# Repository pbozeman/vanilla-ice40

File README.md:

# Vanilla ICE40

Hardware design and verilog sample files for Lattice ICE40
development boards and expansion boards.

## Development Boards

There are 2 core boards, one based on an ICE40 HX4K with 96
available IO pins, and another based on an ICE40 HX8K with
192 available IO pins.

The core boards are "vanilla" with minimal on board peripherals.
Almost all IO pins are routed to mezzanine connectors. Expansion
boards can be mixed and matched for different projects, while reusing
the core board. The expansion boards can be daisy chained.

This is a work in progress for use in a personal project, but so far
the following boards are in the repo:

* **vanilla-ice40**: core board based on the HX4K TQ144 package. There is
an onboard USBC connector for power, programming, and uart/com port
communication. It is directly programmable with Lattice Diamond Programmer
and icestorm. The onboard FTDI chip can be disabled. The SPI pins to the
flash and ice40 are exposed if one wishes to use an external
programmer. There are 2 onboard user LEDs, 1 I2C connector, and 96 IOs
routed to a mezzanine connector on the right side of the board.

* **vanilla-ice40-hx8k**: core board based on the HX8K CT256 BGA package.
It is similar to the board above, but ads a user button on board. It has
192 available IO pins, with 96 IO pins routed to the left and 96 pins routed
to the right of the board. (A PCF file is provided for both boards, sharing
the same signal names for the right side of the board.)

* **breakout-sram**: 16Mbit sram chip with with mezzanine connectors
on both side of the board for pass through of unused pins.

* **breakout-pmod**: 12 port pmod connector, spaced such that they
can be used in single, dual or quad pmod configurations.

* **breakout-passthrough**: direct passthrough of all signals. (This
is basically a template and for testing.) NOTE: the net names and
labels on this board are stale.

Parts numbers are populated for Digikey and JLCPCB, and JLCPCB
rotations are provided. The bom and positions file, along with
gerbers, can be exported with the JLCPCB Fabrication Toolkit
plugin.

All boards other than the HX8K are single sided and optimized for cost
and hand assembly. My soldering skills are below average, and I manged to
hand assemble versions of each of these these boards other than the HX8K.
The HX8K uses BGA, via-in-pad, and 201 sized caps between the BGA pads, and
likely requires higher soldering skills.

## Verilog examples

* Verilog development has moved to <https://github.com/pbozeman/svc> for the core
SVC library, and <https://github.com/pbozeman/svc-example> for examples using
these boards.

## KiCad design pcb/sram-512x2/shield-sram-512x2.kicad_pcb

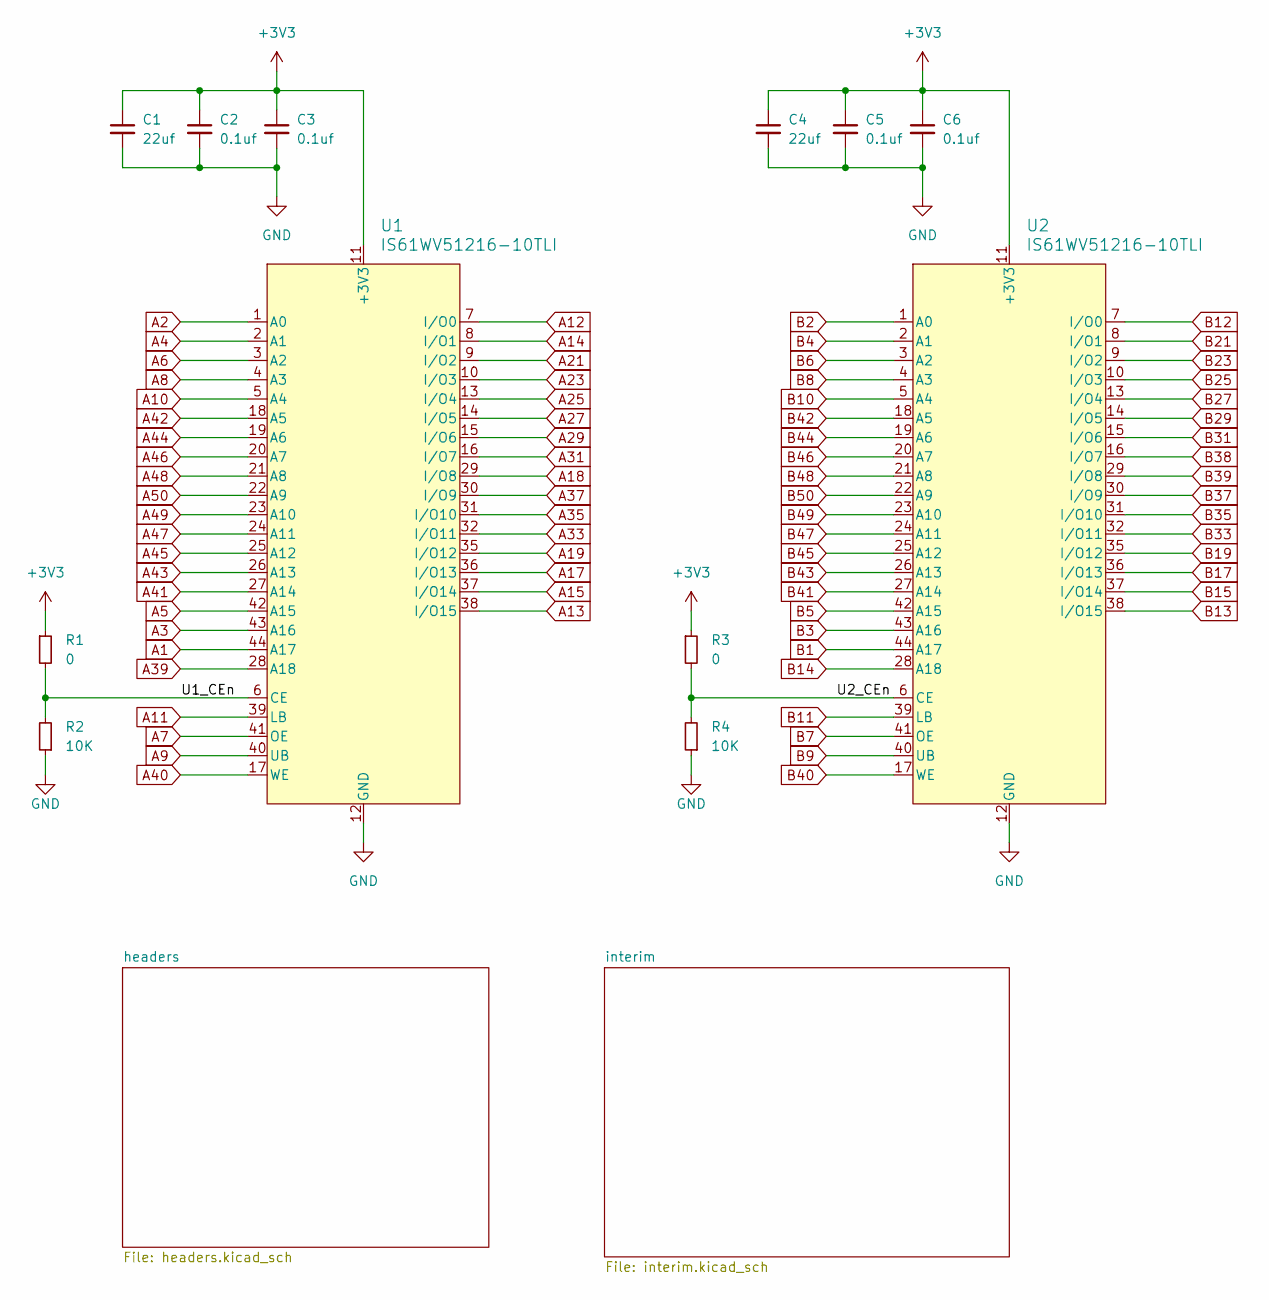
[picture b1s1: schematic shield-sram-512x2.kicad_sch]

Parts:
C1, C4: 22uf; C_0603_1608Metric; LCSC Part # C59461
C2, C3, C5, C6: 0.1uf; C_0402_1005Metric; LCSC Part # C1525
R1, R3: 0; R_0603_1608Metric; LCSC Part # DNP
R2, R4: 10K; R_0603_1608Metric; LCSC Part # C25804
U1, U2: IS61WV51216-10TLI; 44L_TSOP-2_400_ISI; LCSC Part # C397874

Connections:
+3V3: C1.1, C2.1, C3.1, C4.1, C5.1, C6.1, R1.1, R3.1, U1.11 (+3V3), U1.33 (+3V3), U2.11 (+3V3), U2.33 (+3V3); also elsewhere on the board
/U1_CEn: R1.2, R2.2, U1.6 (CE)
/U2_CEn: R3.2, R4.2, U2.6 (CE)
A1: U1.44 (A17); also elsewhere on the board
A2: U1.1 (A0); also elsewhere on the board
A3: U1.43 (A16); also elsewhere on the board
A4: U1.2 (A1); also elsewhere on the board
A5: U1.42 (A15); also elsewhere on the board
A6: U1.3 (A2); also elsewhere on the board
A7: U1.41 (OE); also elsewhere on the board
A8: U1.4 (A3); also elsewhere on the board
A9: U1.40 (UB); also elsewhere on the board
A10: U1.5 (A4); also elsewhere on the board
A11: U1.39 (LB); also elsewhere on the board
A12: U1.7 (I/O0); also elsewhere on the board
A13: U1.38 (I/O15); also elsewhere on the board
A14: U1.8 (I/O1); also elsewhere on the board
A15: U1.37 (I/O14); also elsewhere on the board
A17: U1.36 (I/O13); also elsewhere on the board
A18: U1.29 (I/O8); also elsewhere on the board
A19: U1.35 (I/O12); also elsewhere on the board
A21: U1.9 (I/O2); also elsewhere on the board
A23: U1.10 (I/O3); also elsewhere on the board
A25: U1.13 (I/O4); also elsewhere on the board
A27: U1.14 (I/O5); also elsewhere on the board
A29: U1.15 (I/O6); also elsewhere on the board
A31: U1.16 (I/O7); also elsewhere on the board
A33: U1.32 (I/O11); also elsewhere on the board
A35: U1.31 (I/O10); also elsewhere on the board
A37: U1.30 (I/O9); also elsewhere on the board
A39: U1.28 (A18); also elsewhere on the board
A40: U1.17 (WE); also elsewhere on the board
A41: U1.27 (A14); also elsewhere on the board
A42: U1.18 (A5); also elsewhere on the board
A43: U1.26 (A13); also elsewhere on the board
A44: U1.19 (A6); also elsewhere on the board
A45: U1.25 (A12); also elsewhere on the board
A46: U1.20 (A7); also elsewhere on the board
A47: U1.24 (A11); also elsewhere on the board
A48: U1.21 (A8); also elsewhere on the board
A49: U1.23 (A10); also elsewhere on the board
A50: U1.22 (A9); also elsewhere on the board
B1: U2.44 (A17); also elsewhere on the board
B2: U2.1 (A0); also elsewhere on the board
B3: U2.43 (A16); also elsewhere on the board
B4: U2.2 (A1); also elsewhere on the board
B5: U2.42 (A15); also elsewhere on the board
B6: U2.3 (A2); also elsewhere on the board
B7: U2.41 (OE); also elsewhere on the board
B8: U2.4 (A3); also elsewhere on the board
B9: U2.40 (UB); also elsewhere on the board
B10: U2.5 (A4); also elsewhere on the board
B11: U2.39 (LB); also elsewhere on the board
B12: U2.7 (I/O0); also elsewhere on the board
B13: U2.38 (I/O15); also elsewhere on the board
B14: U2.28 (A18); also elsewhere on the board
B15: U2.37 (I/O14); also elsewhere on the board
B17: U2.36 (I/O13); also elsewhere on the board
B19: U2.35 (I/O12); also elsewhere on the board
B21: U2.8 (I/O1); also elsewhere on the board
B23: U2.9 (I/O2); also elsewhere on the board
B25: U2.10 (I/O3); also elsewhere on the board
B27: U2.13 (I/O4); also elsewhere on the board
B29: U2.14 (I/O5); also elsewhere on the board
B31: U2.15 (I/O6); also elsewhere on the board
B33: U2.32 (I/O11); also elsewhere on the board
B35: U2.31 (I/O10); also elsewhere on the board
B37: U2.30 (I/O9); also elsewhere on the board
B38: U2.16 (I/O7); also elsewhere on the board
B39: U2.29 (I/O8); also elsewhere on the board
B40: U2.17 (WE); also elsewhere on the board
B41: U2.27 (A14); also elsewhere on the board
B42: U2.18 (A5); also elsewhere on the board
B43: U2.26 (A13); also elsewhere on the board
B44: U2.19 (A6); also elsewhere on the board
B45: U2.25 (A12); also elsewhere on the board
B46: U2.20 (A7); also elsewhere on the board
B47: U2.24 (A11); also elsewhere on the board
B48: U2.21 (A8); also elsewhere on the board
B49: U2.23 (A10); also elsewhere on the board
B50: U2.22 (A9); also elsewhere on the board
GND: C1.2, C2.2, C3.2, C4.2, C5.2, C6.2, R2.1, R4.1, U1.12 (GND), U1.34 (GND), U2.12 (GND), U2.34 (GND); also elsewhere on the board

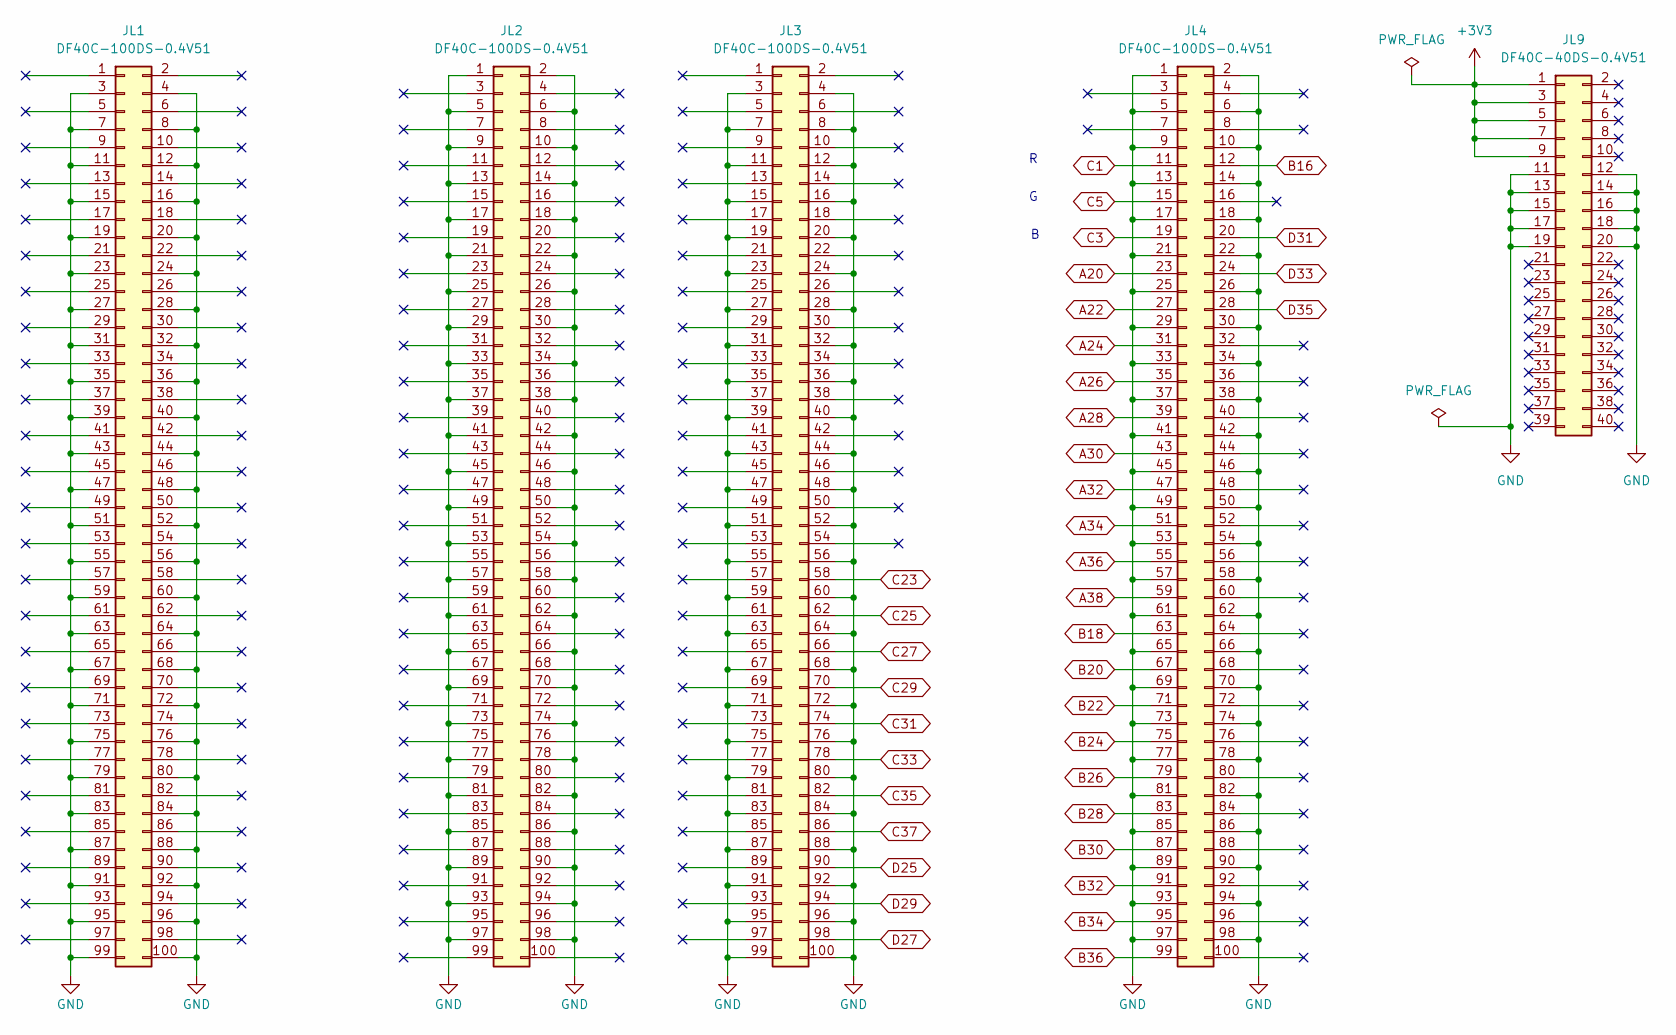
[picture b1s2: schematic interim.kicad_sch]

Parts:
JL1, JL2, JL3, JL4: DF40C-100DS-0.4V51; DF40C100DS04V51; Digi-Key Part Number H11615CT-ND
JL9: DF40C-40DS-0.4V51; DF40C40DS04V51; Digi-Key Part Number H11625CT-ND

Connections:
+3V3: JL9.1, JL9.3, JL9.5, JL9.7, JL9.9; also elsewhere on the board
A20: JL4.23; also elsewhere on the board
A22: JL4.27; also elsewhere on the board
A24: JL4.31; also elsewhere on the board
A26: JL4.35; also elsewhere on the board
A28: JL4.39; also elsewhere on the board
A30: JL4.43; also elsewhere on the board
A32: JL4.47; also elsewhere on the board
A34: JL4.51; also elsewhere on the board
A36: JL4.55; also elsewhere on the board
A38: JL4.59; also elsewhere on the board
B16: JL4.12; also elsewhere on the board
B18: JL4.63; also elsewhere on the board
B20: JL4.67; also elsewhere on the board
B22: JL4.71; also elsewhere on the board
B24: JL4.75; also elsewhere on the board
B26: JL4.79; also elsewhere on the board
B28: JL4.83; also elsewhere on the board
B30: JL4.87; also elsewhere on the board
B32: JL4.91; also elsewhere on the board
B34: JL4.95; also elsewhere on the board
B36: JL4.99; also elsewhere on the board
C1: JL4.11; also elsewhere on the board
C3: JL4.19; also elsewhere on the board
C5: JL4.15; also elsewhere on the board
C23: JL3.58; also elsewhere on the board
C25: JL3.62; also elsewhere on the board
C27: JL3.66; also elsewhere on the board
C29: JL3.70; also elsewhere on the board
C31: JL3.74; also elsewhere on the board
C33: JL3.78; also elsewhere on the board
C35: JL3.82; also elsewhere on the board
C37: JL3.86; also elsewhere on the board
D25: JL3.90; also elsewhere on the board
D27: JL3.98; also elsewhere on the board
D29: JL3.94; also elsewhere on the board
D31: JL4.20; also elsewhere on the board
D33: JL4.24; also elsewhere on the board
D35: JL4.28; also elsewhere on the board
GND: JL1.3, JL1.4, JL1.7, JL1.8, JL1.11, JL1.12, JL1.15, JL1.16, JL1.19, JL1.20, JL1.23, JL1.24, JL1.27, JL1.28, JL1.31, JL1.32, JL1.35, JL1.36, JL1.39, JL1.40, JL1.43, JL1.44, JL1.47, JL1.48, JL1.51, JL1.52, JL1.55, JL1.56, JL1.59, JL1.60, JL1.63, JL1.64, JL1.67, JL1.68, JL1.71, JL1.72, JL1.75, JL1.76, JL1.79, JL1.80, JL1.83, JL1.84, JL1.87, JL1.88, JL1.91, JL1.92, JL1.95, JL1.96, JL1.99, JL1.100, JL2.1, JL2.2, JL2.5, JL2.6, JL2.9, JL2.10, JL2.13, JL2.14, JL2.17, JL2.18, JL2.21, JL2.22, JL2.25, JL2.26, JL2.29, JL2.30, JL2.33, JL2.34, JL2.37, JL2.38, JL2.41, JL2.42, JL2.45, JL2.46, JL2.49, JL2.50, JL2.53, JL2.54, JL2.57, JL2.58, JL2.61, JL2.62, JL2.65, JL2.66, JL2.69, JL2.70, JL2.73, JL2.74, JL2.77, JL2.78, JL2.81, JL2.82, JL2.85, JL2.86, JL2.89, JL2.90, JL2.93, JL2.94, JL2.97, JL2.98, JL3.3, JL3.4, JL3.7, JL3.8, JL3.11, JL3.12, JL3.15, JL3.16, JL3.19, JL3.20, JL3.23, JL3.24, JL3.27, JL3.28, JL3.31, JL3.32, JL3.35, JL3.36, JL3.39, JL3.40, JL3.43, JL3.44, JL3.47, JL3.48, JL3.51, JL3.52, JL3.55, JL3.56, JL3.59, JL3.60, JL3.63, JL3.64, JL3.67, JL3.68, JL3.71, JL3.72, JL3.75, JL3.76, JL3.79, JL3.80, JL3.83, JL3.84, JL3.87, JL3.88, JL3.91, JL3.92, JL3.95, JL3.96, JL3.99, JL3.100, JL4.1, JL4.2, JL4.5, JL4.6, JL4.9, JL4.10, JL4.13, JL4.14, JL4.17, JL4.18, JL4.21, JL4.22, JL4.25, JL4.26, JL4.29, JL4.30, JL4.33, JL4.34, JL4.37, JL4.38, JL4.41, JL4.42, JL4.45, JL4.46, JL4.49, JL4.50, JL4.53, JL4.54, JL4.57, JL4.58, JL4.61, JL4.62, JL4.65, JL4.66, JL4.69, JL4.70, JL4.73, JL4.74, JL4.77, JL4.78, JL4.81, JL4.82, JL4.85, JL4.86, JL4.89, JL4.90, JL4.93, JL4.94, JL4.97, JL4.98, JL9.11, JL9.12, JL9.13, JL9.14, JL9.15, JL9.16, JL9.17, JL9.18, JL9.19, JL9.20; also elsewhere on the board

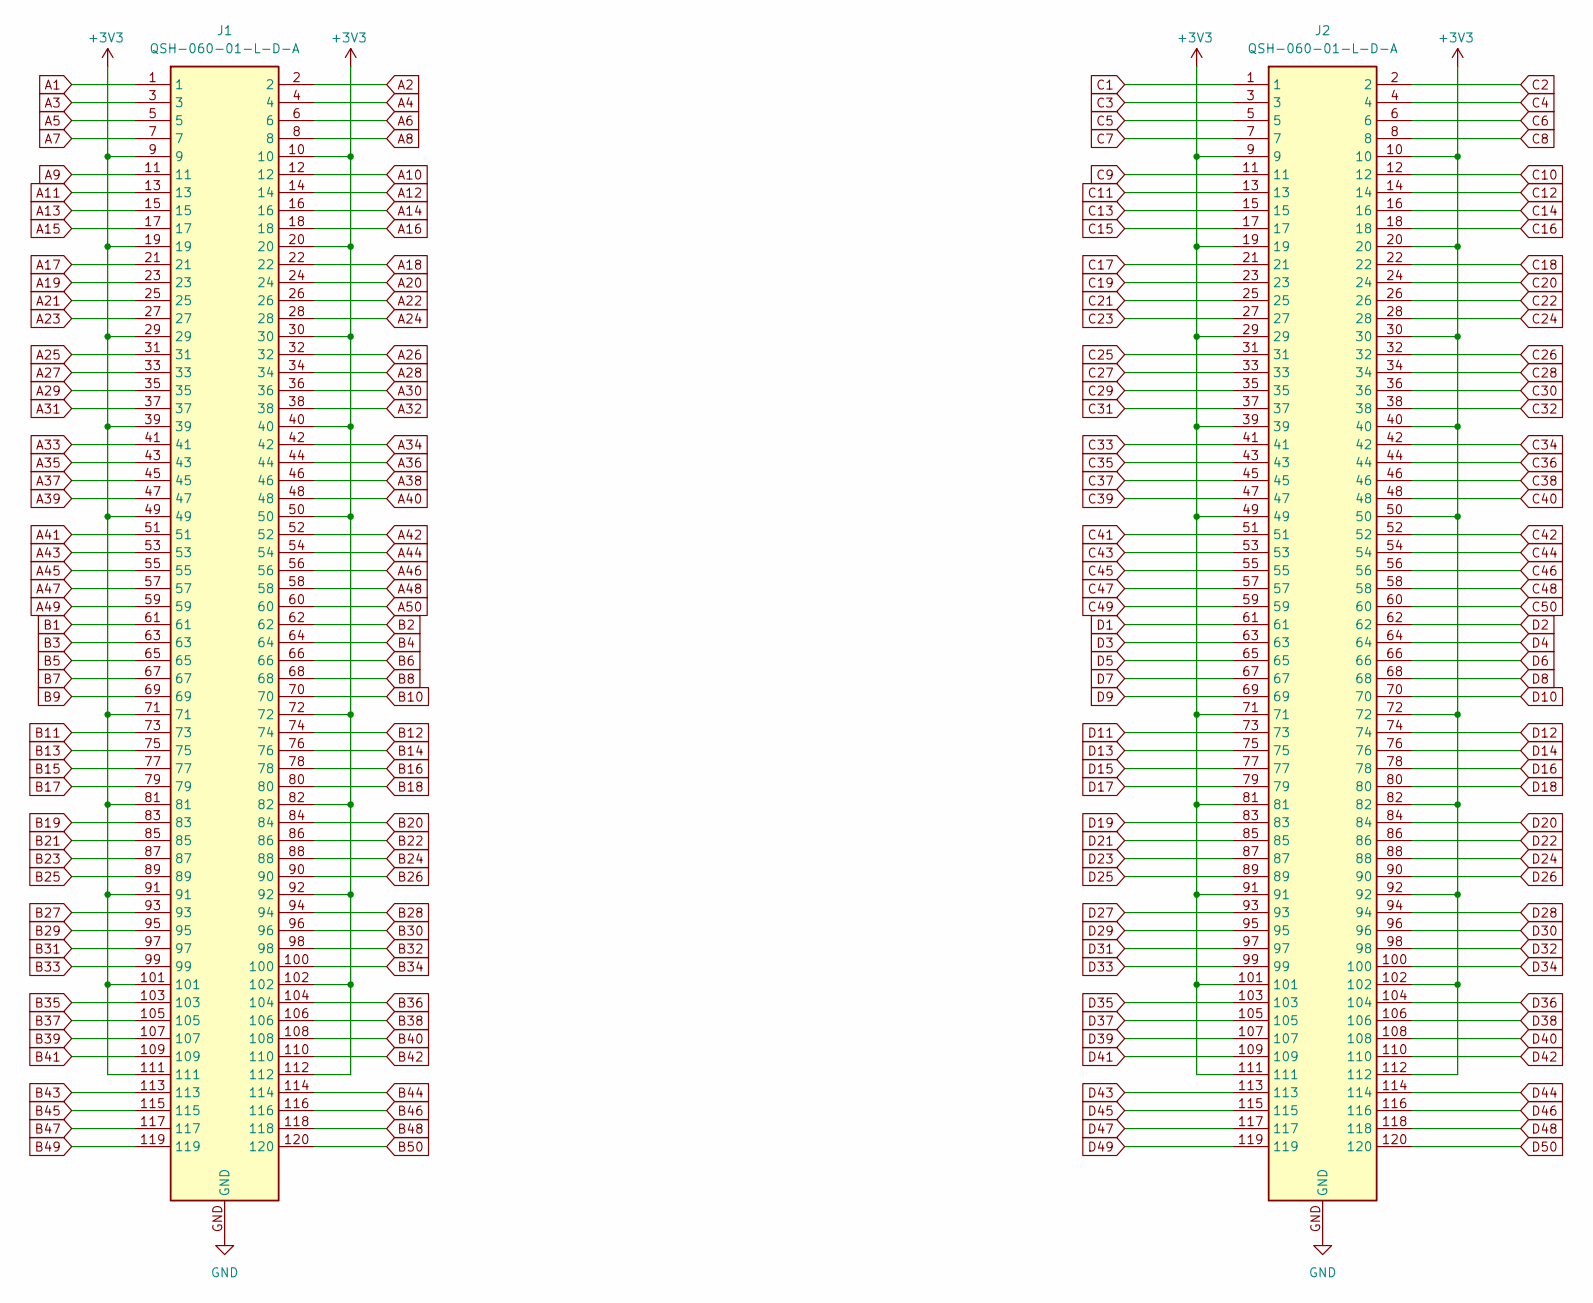
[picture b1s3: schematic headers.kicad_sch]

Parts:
J1, J2: QSH-060-01-L-D-A; SAMTEC_QSH-060-01-X-D-A

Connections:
+3V3: J1.9, J1.10, J1.19, J1.20, J1.29, J1.30, J1.39, J1.40, J1.49, J1.50, J1.71, J1.72, J1.81, J1.82, J1.91, J1.92, J1.101, J1.102, J1.111, J1.112, J2.9, J2.10, J2.19, J2.20, J2.29, J2.30, J2.39, J2.40, J2.49, J2.50, J2.71, J2.72, J2.81, J2.82, J2.91, J2.92, J2.101, J2.102, J2.111, J2.112; also elsewhere on the board
A1: J1.1; also elsewhere on the board
A2: J1.2; also elsewhere on the board
A3: J1.3; also elsewhere on the board
A4: J1.4; also elsewhere on the board
A5: J1.5; also elsewhere on the board
A6: J1.6; also elsewhere on the board
A7: J1.7; also elsewhere on the board
A8: J1.8; also elsewhere on the board
A9: J1.11; also elsewhere on the board
A10: J1.12; also elsewhere on the board
A11: J1.13; also elsewhere on the board
A12: J1.14; also elsewhere on the board
A13: J1.15; also elsewhere on the board
A14: J1.16; also elsewhere on the board
A15: J1.17; also elsewhere on the board
A16: J1.18
A17: J1.21; also elsewhere on the board
A18: J1.22; also elsewhere on the board
A19: J1.23; also elsewhere on the board
A20: J1.24; also elsewhere on the board
A21: J1.25; also elsewhere on the board
A22: J1.26; also elsewhere on the board
A23: J1.27; also elsewhere on the board
A24: J1.28; also elsewhere on the board
A25: J1.31; also elsewhere on the board
A26: J1.32; also elsewhere on the board
A27: J1.33; also elsewhere on the board
A28: J1.34; also elsewhere on the board
A29: J1.35; also elsewhere on the board
A30: J1.36; also elsewhere on the board
A31: J1.37; also elsewhere on the board
A32: J1.38; also elsewhere on the board
A33: J1.41; also elsewhere on the board
A34: J1.42; also elsewhere on the board
A35: J1.43; also elsewhere on the board
A36: J1.44; also elsewhere on the board
A37: J1.45; also elsewhere on the board
A38: J1.46; also elsewhere on the board
A39: J1.47; also elsewhere on the board
A40: J1.48; also elsewhere on the board
A41: J1.51; also elsewhere on the board
A42: J1.52; also elsewhere on the board
A43: J1.53; also elsewhere on the board
A44: J1.54; also elsewhere on the board
A45: J1.55; also elsewhere on the board
A46: J1.56; also elsewhere on the board
A47: J1.57; also elsewhere on the board
A48: J1.58; also elsewhere on the board
A49: J1.59; also elsewhere on the board
A50: J1.60; also elsewhere on the board
B1: J1.61; also elsewhere on the board
B2: J1.62; also elsewhere on the board
B3: J1.63; also elsewhere on the board
B4: J1.64; also elsewhere on the board
B5: J1.65; also elsewhere on the board
B6: J1.66; also elsewhere on the board
B7: J1.67; also elsewhere on the board
B8: J1.68; also elsewhere on the board
B9: J1.69; also elsewhere on the board
B10: J1.70; also elsewhere on the board
B11: J1.73; also elsewhere on the board
B12: J1.74; also elsewhere on the board
B13: J1.75; also elsewhere on the board
B14: J1.76; also elsewhere on the board
B15: J1.77; also elsewhere on the board
B16: J1.78; also elsewhere on the board
B17: J1.79; also elsewhere on the board
B18: J1.80; also elsewhere on the board
B19: J1.83; also elsewhere on the board
B20: J1.84; also elsewhere on the board
B21: J1.85; also elsewhere on the board
B22: J1.86; also elsewhere on the board
B23: J1.87; also elsewhere on the board
B24: J1.88; also elsewhere on the board
B25: J1.89; also elsewhere on the board
B26: J1.90; also elsewhere on the board
B27: J1.93; also elsewhere on the board
B28: J1.94; also elsewhere on the board
B29: J1.95; also elsewhere on the board
B30: J1.96; also elsewhere on the board
B31: J1.97; also elsewhere on the board
B32: J1.98; also elsewhere on the board
B33: J1.99; also elsewhere on the board
B34: J1.100; also elsewhere on the board
B35: J1.103; also elsewhere on the board
B36: J1.104; also elsewhere on the board
B37: J1.105; also elsewhere on the board
B38: J1.106; also elsewhere on the board
B39: J1.107; also elsewhere on the board
B40: J1.108; also elsewhere on the board
B41: J1.109; also elsewhere on the board
B42: J1.110; also elsewhere on the board
B43: J1.113; also elsewhere on the board
B44: J1.114; also elsewhere on the board
B45: J1.115; also elsewhere on the board
B46: J1.116; also elsewhere on the board
B47: J1.117; also elsewhere on the board
B48: J1.118; also elsewhere on the board
B49: J1.119; also elsewhere on the board
B50: J1.120; also elsewhere on the board
C1: J2.1; also elsewhere on the board
C2: J2.2
C3: J2.3; also elsewhere on the board
C4: J2.4
C5: J2.5; also elsewhere on the board
C6: J2.6
C7: J2.7
C8: J2.8
C9: J2.11
C10: J2.12
C11: J2.13
C12: J2.14
C13: J2.15
C14: J2.16
C15: J2.17
C16: J2.18
C17: J2.21
C18: J2.22
C19: J2.23
C20: J2.24
C21: J2.25
C22: J2.26
C23: J2.27; also elsewhere on the board
C24: J2.28
C25: J2.31; also elsewhere on the board
C26: J2.32
C27: J2.33; also elsewhere on the board
C28: J2.34
C29: J2.35; also elsewhere on the board
C30: J2.36
C31: J2.37; also elsewhere on the board
C32: J2.38
C33: J2.41; also elsewhere on the board
C34: J2.42
C35: J2.43; also elsewhere on the board
C36: J2.44
C37: J2.45; also elsewhere on the board
C38: J2.46
C39: J2.47
C40: J2.48
C41: J2.51
C42: J2.52
C43: J2.53
C44: J2.54
C45: J2.55
C46: J2.56
C47: J2.57
C48: J2.58
C49: J2.59
C50: J2.60
D1: J2.61
D2: J2.62
D3: J2.63
D4: J2.64
D5: J2.65
D6: J2.66
D7: J2.67
D8: J2.68
D9: J2.69
D10: J2.70
D11: J2.73
D12: J2.74
D13: J2.75
D14: J2.76
D15: J2.77
D16: J2.78
D17: J2.79
D18: J2.80
D19: J2.83
D20: J2.84
D21: J2.85
D22: J2.86
D23: J2.87
D24: J2.88
D25: J2.89; also elsewhere on the board
D26: J2.90
D27: J2.93; also elsewhere on the board
D28: J2.94
D29: J2.95; also elsewhere on the board
D30: J2.96
D31: J2.97; also elsewhere on the board
D32: J2.98
D33: J2.99; also elsewhere on the board
D34: J2.100
D35: J2.103; also elsewhere on the board
D36: J2.104
D37: J2.105
D38: J2.106
D39: J2.107
D40: J2.108
D41: J2.109
D42: J2.110
D43: J2.113
D44: J2.114
D45: J2.115
D46: J2.116
D47: J2.117
D48: J2.118
D49: J2.119
D50: J2.120
GND: J1.GND, J2.GND; also elsewhere on the board

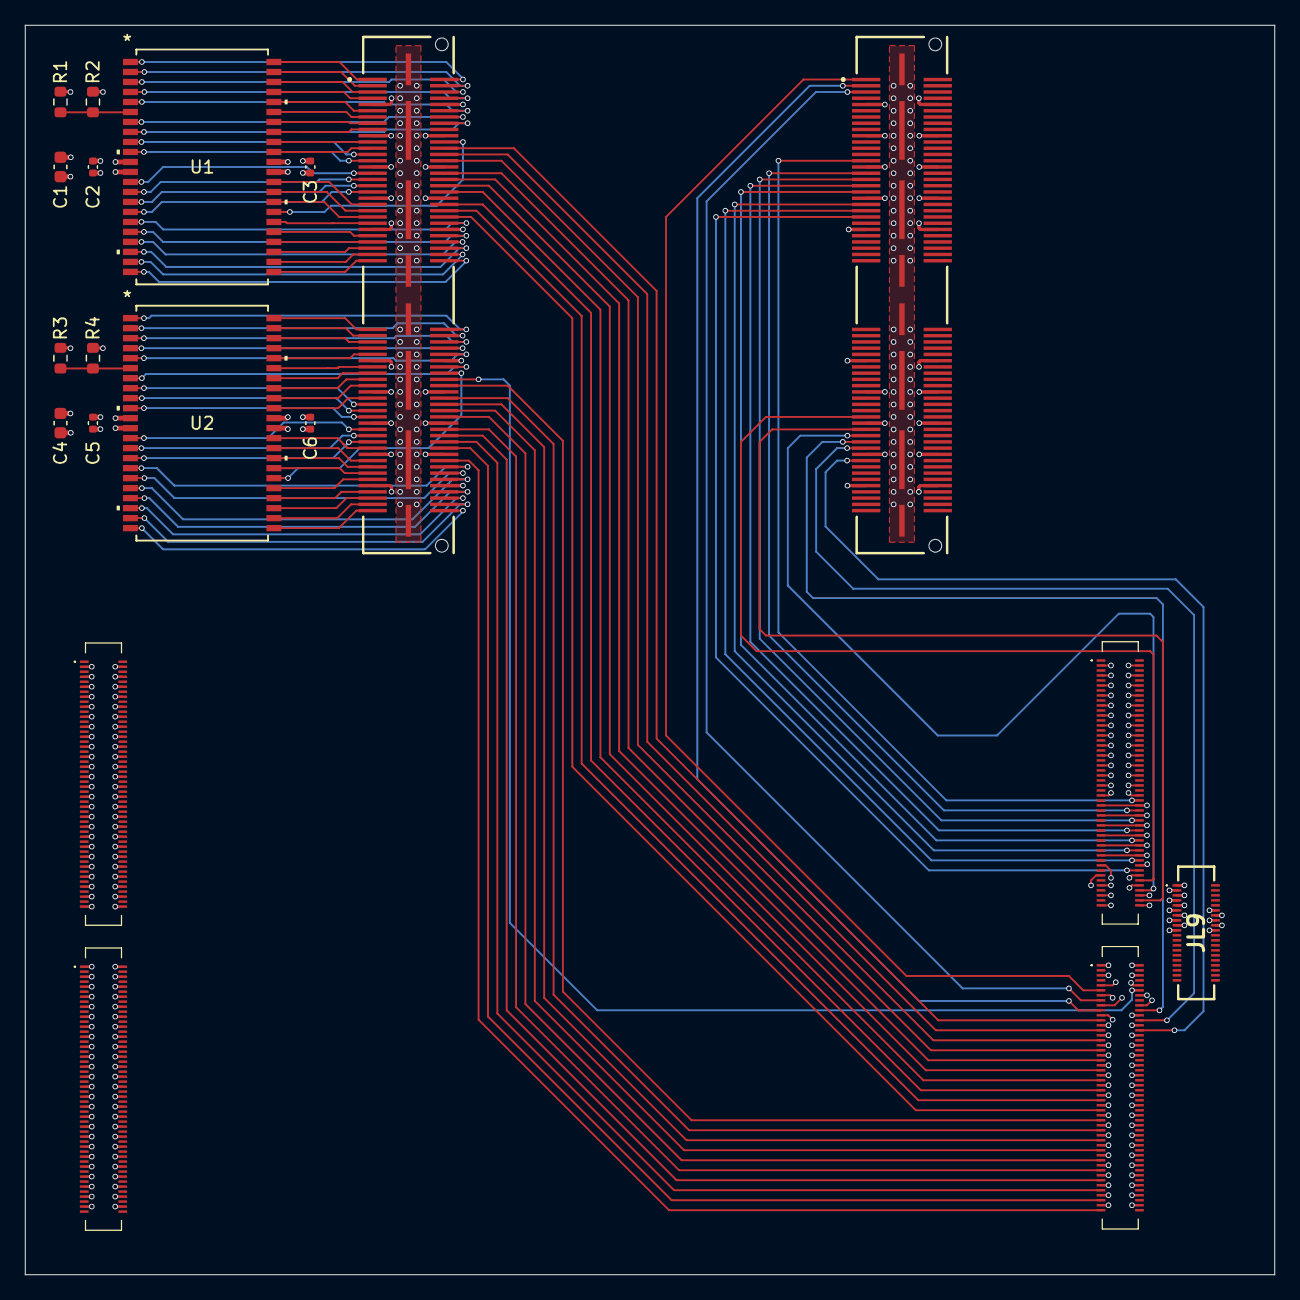
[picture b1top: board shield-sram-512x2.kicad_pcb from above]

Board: 4 copper layers, 100.0 x 100.0 mm, 19 parts (0 on the bottom side), 120 nets.

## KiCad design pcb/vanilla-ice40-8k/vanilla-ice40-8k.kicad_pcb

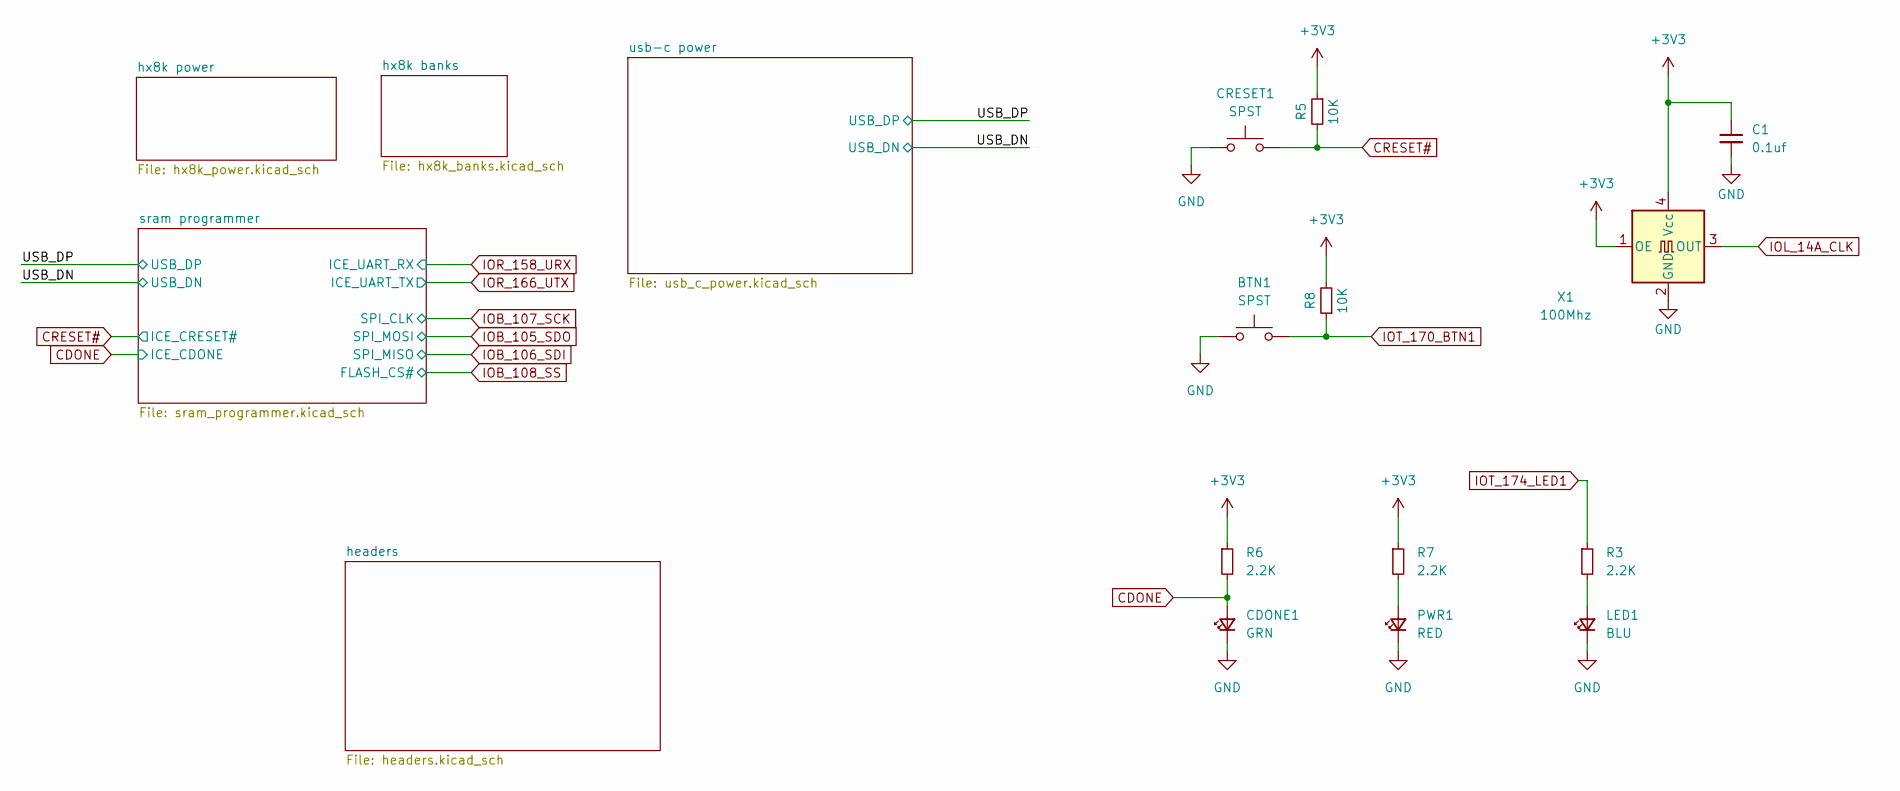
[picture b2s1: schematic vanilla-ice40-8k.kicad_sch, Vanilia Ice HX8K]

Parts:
BTN1: SPST; SW_SPST_PTS810; LCSC Part # C221897
C1: 0.1uf; C_0402_1005Metric; LCSC Part # C1525
CDONE1: GRN; D_0603_1608Metric; LCSC Part # C434423
CRESET1: SPST; SW_SPST_PTS810; LCSC Part # C221897
LED1: BLU; D_0603_1608Metric; LCSC Part # C434421
PWR1: RED; D_0603_1608Metric; LCSC Part # C434419
R3, R6, R7: 2.2K; R_0603_1608Metric; LCSC Part # C4190
R5, R8: 10K; R_0603_1608Metric; LCSC Part # C25804
X1: 100Mhz; Oscillator_SMD_SeikoEpson_SG8002CE-4Pin_3.2x2.5mm; LCSC Part # C390559

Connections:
+3V3: C1.1, R5.1, R6.1, R7.1, R8.2, X1.1 (OE), X1.4 (Vcc); also elsewhere on the board
CDONE: CDONE1.2 (A), R6.2; also elsewhere on the board
CRESET#: CRESET1.2, R5.2; also elsewhere on the board
GND: BTN1.1, C1.2, CDONE1.1 (K), CRESET1.1, LED1.1 (K), PWR1.1 (K), X1.2 (GND); also elsewhere on the board
IOL_14A_CLK: X1.3 (OUT); also elsewhere on the board
IOT_170_BTN1: BTN1.2, R8.1; also elsewhere on the board
IOT_174_LED1: R3.1; also elsewhere on the board
unnamed: LED1.2 (A), R3.2
unnamed: PWR1.2 (A), R7.2

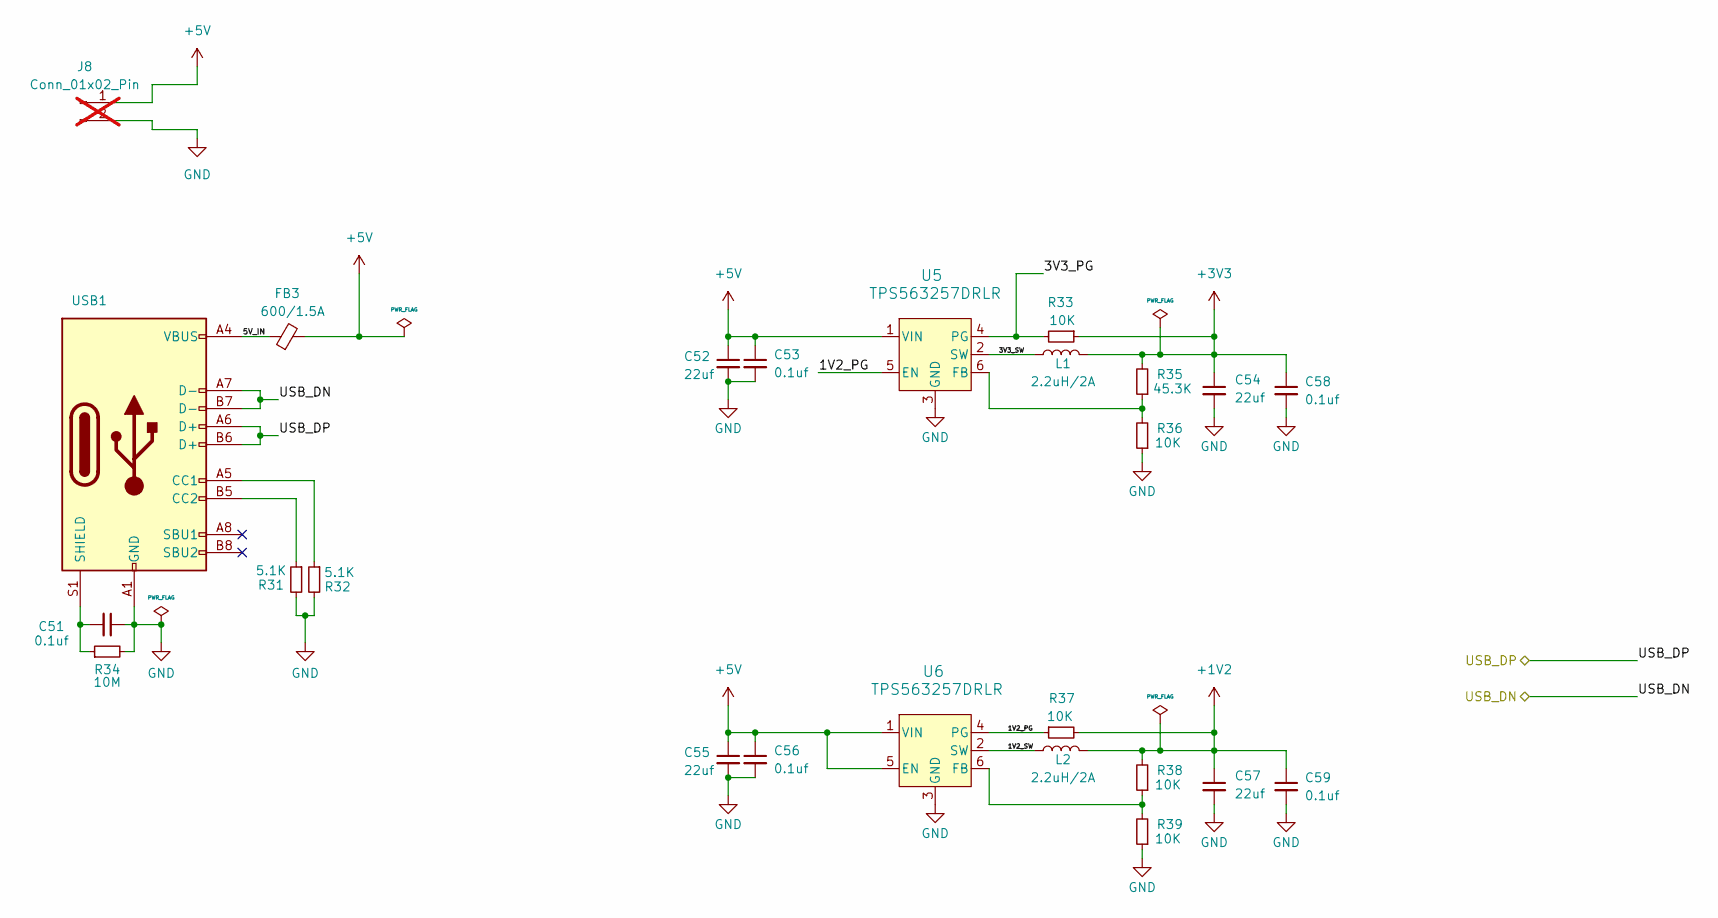
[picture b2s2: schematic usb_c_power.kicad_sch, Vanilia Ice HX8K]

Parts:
C51, C53, C56, C58, C59: 0.1uf; C_0402_1005Metric; LCSC Part # C1525
C52, C54, C55, C57: 22uf; C_0603_1608Metric; LCSC Part # C59461
FB3: 600/1.5A; L_1206_3216Metric; LCSC Part # C16902
J8: Conn_01x02_Pin; not fitted
L1, L2: 2.2uH/2A; L_1008_2520Metric; LCSC Part # C576403
R31, R32: 5.1K; R_0603_1608Metric; LCSC Part # C23186
R33, R36, R37, R38, R39: 10K; R_0603_1608Metric; LCSC Part # C25804
R34: 10M; R_0603_1608Metric; LCSC Part # C7250
R35: 45.3K; R_0603_1608Metric; LCSC Part # C23058
U5, U6: TPS563257DRLR; SOT6_DRL_TEX; LCSC Part # C20539656
USB1: USB_C_Receptacle_USB2.0_16P; USB_C_Receptacle_GCT_USB4105-xx-A_16P_TopMnt_Horizontal; LCSC Part # C2686968

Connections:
+1V2: C57.1, C59.1, L2.2, R37.2, R38.2; also elsewhere on the board
+3V3: C54.1, C58.1, L1.2, R33.1, R35.2; also elsewhere on the board
+5V: C52.1, C53.1, C55.1, C56.1, FB3.2, J8.1, U5.1 (VIN), U6.1 (VIN), U6.5 (EN)
/USB_DN: USB1.A7 (D-), USB1.B7 (D-); also elsewhere on the board
/USB_DP: USB1.A6 (D+), USB1.B6 (D+); also elsewhere on the board
/usb-c power/1V2_PG: R37.1, U5.5 (EN), U6.4 (PG)
/usb-c power/1V2_SW: L2.1, U6.2 (SW)
/usb-c power/3V3_PG: R33.2, U5.4 (PG)
/usb-c power/3V3_SW: L1.1, U5.2 (SW)
/usb-c power/5V_IN: FB3.1, USB1.A4 (VBUS), USB1.A9 (VBUS), USB1.B4 (VBUS), USB1.B9 (VBUS)
GND: C51.1, C52.2, C53.2, C54.2, C55.2, C56.2, C57.2, C58.2, C59.2, J8.2, R31.2, R32.2, R34.2, R36.1, R39.1, U5.3 (GND), U6.3 (GND), USB1.A1 (GND), USB1.A12 (GND), USB1.B1 (GND), USB1.B12 (GND); also elsewhere on the board
unnamed: R35.1, R36.2, U5.6 (FB)
unnamed: R38.1, R39.2, U6.6 (FB)
unnamed: R32.1, USB1.A5 (CC1)
unnamed: R31.1, USB1.B5 (CC2)
unnamed: C51.2, R34.1, USB1.S1 (SHIELD)
